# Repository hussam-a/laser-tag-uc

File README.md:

# laser-tag-uc
Microcontroller-based Laser Tag system

Authors:

Hussam A. El-Araby (github.com/hussam-a)

Mostafa Konsowa (github.com/konsowa)

Youssef Gaber (github.com/Gabrola)

Mennatallah Yahia

Ziad Osama

Project code and configurations are under the GNU GPL license (laser-tag-uc/LICENSE) 

# Project structure:

- Check files under folder project (laser-tag-uc/project)

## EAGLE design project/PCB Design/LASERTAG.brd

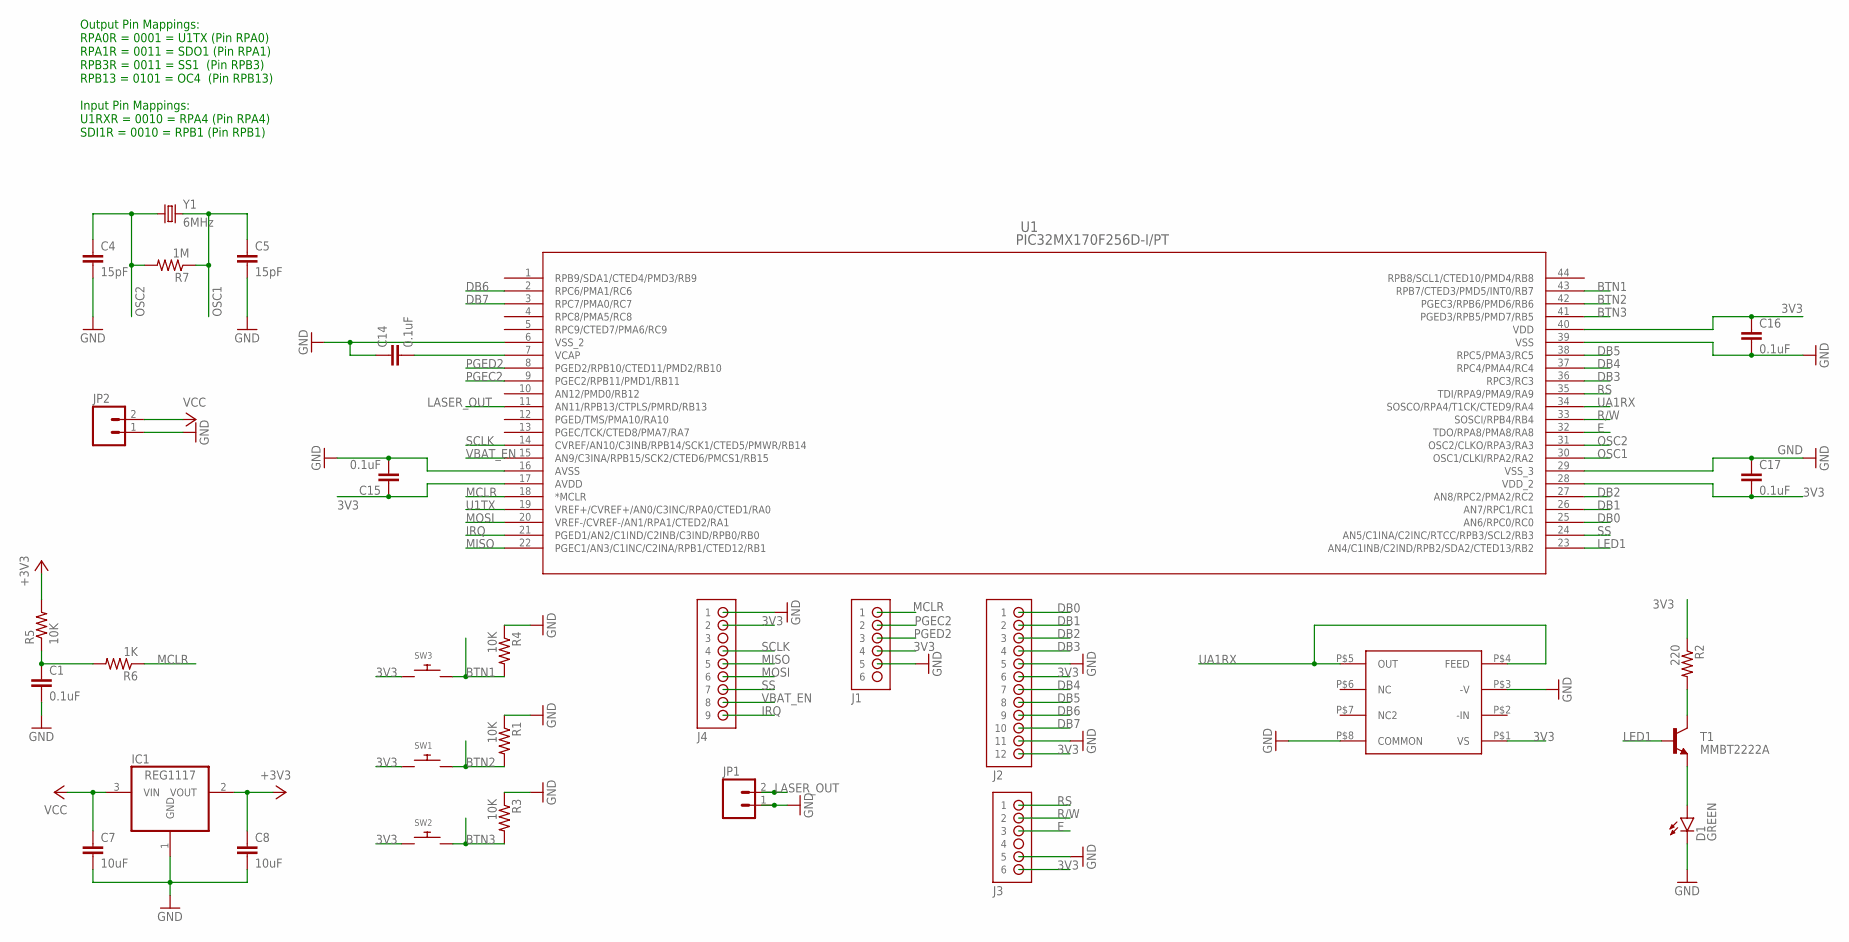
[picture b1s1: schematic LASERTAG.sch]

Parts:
C1, C14, C15, C16, C17: 0.1uF; 0603-CAP
C4, C5: 15pF; 0603-CAP
C7, C8: 10uF; 0603-CAP
D1: GREEN; LED-0603
IC1: REG1117; SOT223
IC3: OPT101P
J1, J3: HDR-1X6
J2: PMOD-2X6-P
J4: HDR-1X9
JP1, JP2: M02JST-PTH-2; JST-2-PTH
R1, R3, R4, R5: 10K; 0603-RES
R2: 220; 0603-RES
R6: 1K; 0603-RES
R7: 1M; 0603-RES
SW1, SW2, SW3: SWITCH_PUSHBUTTONC&K_KSS; BTN_CK_KSS
T1: MMBT2222A; SOT23
U1: PIC32MX170F256D-I/PT; TQFP44_10X10MC
Y1: 6MHz; HC49US

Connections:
3V3: C8.1, C15.1, C16.1, C17.2, IC1.2 (VOUT), IC3.P$1 (VS), J1.4, J2.6, J2.12, J3.6, J4.2, R2.1, R5.2, SW1.P$1, SW2.P$1, SW3.P$1, U1.17 (AVDD), U1.28 (VDD_2), U1.40 (VDD)
BTN1: R4.2, SW3.P$2, U1.43 (RPB7/CTED3/PMD5/INT0/RB7)
BTN2: R1.2, SW1.P$2, U1.42 (PGEC3/RPB6/PMD6/RB6)
BTN3: R3.2, SW2.P$2, U1.41 (PGED3/RPB5/PMD7/RB5)
DB0: J2.1, U1.25 (AN6/RPC0/RC0)
DB1: J2.2, U1.26 (AN7/RPC1/RC1)
DB2: J2.3, U1.27 (AN8/RPC2/PMA2/RC2)
DB3: J2.4, U1.36 (RPC3/RC3)
DB4: J2.7, U1.37 (RPC4/PMA4/RC4)
DB5: J2.8, U1.38 (RPC5/PMA3/RC5)
DB6: J2.9, U1.2 (RPC6/PMA1/RC6)
DB7: J2.10, U1.3 (RPC7/PMA0/RC7)
E: J3.3, U1.32 (TDO/RPA8/PMA8/RA8)
GND: C1.2, C4.2, C5.2, C7.2, C8.2, C14.1, C15.2, C16.2, C17.1, D1.C, IC1.1 (GND), IC3.P$3 (-V), IC3.P$8 (COMMON), J1.5, J2.5, J2.11, J3.5, J4.1, JP1.1, JP2.1, R1.1, R3.1, R4.1, U1.6 (VSS_2), U1.16 (AVSS), U1.29 (VSS_3), U1.39 (VSS)
IRQ: J4.9, U1.21 (PGED1/AN2/C1IND/C2INB/C3IND/RPB0/RB0)
LASER_OUT: JP1.2, U1.11 (AN11/RPB13/CTPLS/PMRD/RB13)
LED1: T1.1 (B), U1.23 (AN4/C1INB/C2IND/RPB2/SDA2/CTED13/RB2)
MCLR: J1.1, R6.1, U1.18 (*MCLR)
MISO: J4.5, U1.22 (PGEC1/AN3/C1INC/C2INA/RPB1/CTED12/RB1)
MOSI: J4.6, U1.20 (VREF-/CVREF-/AN1/RPA1/CTED2/RA1)
unnamed: C1.1, R5.1, R6.2
unnamed: C14.2, U1.7 (VCAP)
unnamed: R2.2, T1.3 (C)
unnamed: D1.A, T1.2 (E)
OSC1: C5.1, R7.1, U1.30 (OSC1/CLKI/RPA2/RA2), Y1.2
OSC2: C4.1, R7.2, U1.31 (OSC2/CLKO/RPA3/RA3), Y1.1
PGEC2: J1.2, U1.9 (PGEC2/RPB11/PMD1/RB11)
PGED2: J1.3, U1.8 (PGED2/RPB10/CTED11/PMD2/RB10)
R/W: J3.2, U1.33 (SOSCI/RPB4/RB4)
RS: J3.1, U1.35 (TDI/RPA9/PMA9/RA9)
SCLK: J4.4, U1.14 (CVREF/AN10/C3INB/RPB14/SCK1/CTED5/PMWR/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)
SS: J4.7, U1.24 (AN5/C1INA/C2INC/RTCC/RPB3/SCL2/RB3)
U1TX: U1.19 (VREF+/CVREF+/AN0/C3INC/RPA0/CTED1/RA0)
UA1RX: IC3.P$4 (FEED), IC3.P$5 (OUT), U1.34 (SOSCO/RPA4/T1CK/CTED9/RA4)
VBAT_EN: J4.8, U1.15 (AN9/C3INA/RPB15/SCK2/CTED6/PMCS1/RB15)
VCC: C7.1, IC1.3 (VIN), JP2.2

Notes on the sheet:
Output Pin Mappings: RPA0R = 0001 = U1TX (Pin RPA0) RPA1R = 0011 = SDO1 (Pin RPA1) RPB3R = 0011 = SS1 (Pin RPB3) RPB13 = 0101 = OC4 (Pin RPB13) Input Pin Mappings: U1RXR = 0010 = RPA4 (Pin RPA4) SDI1R = 0010 = RPB1 (Pin RPB1)

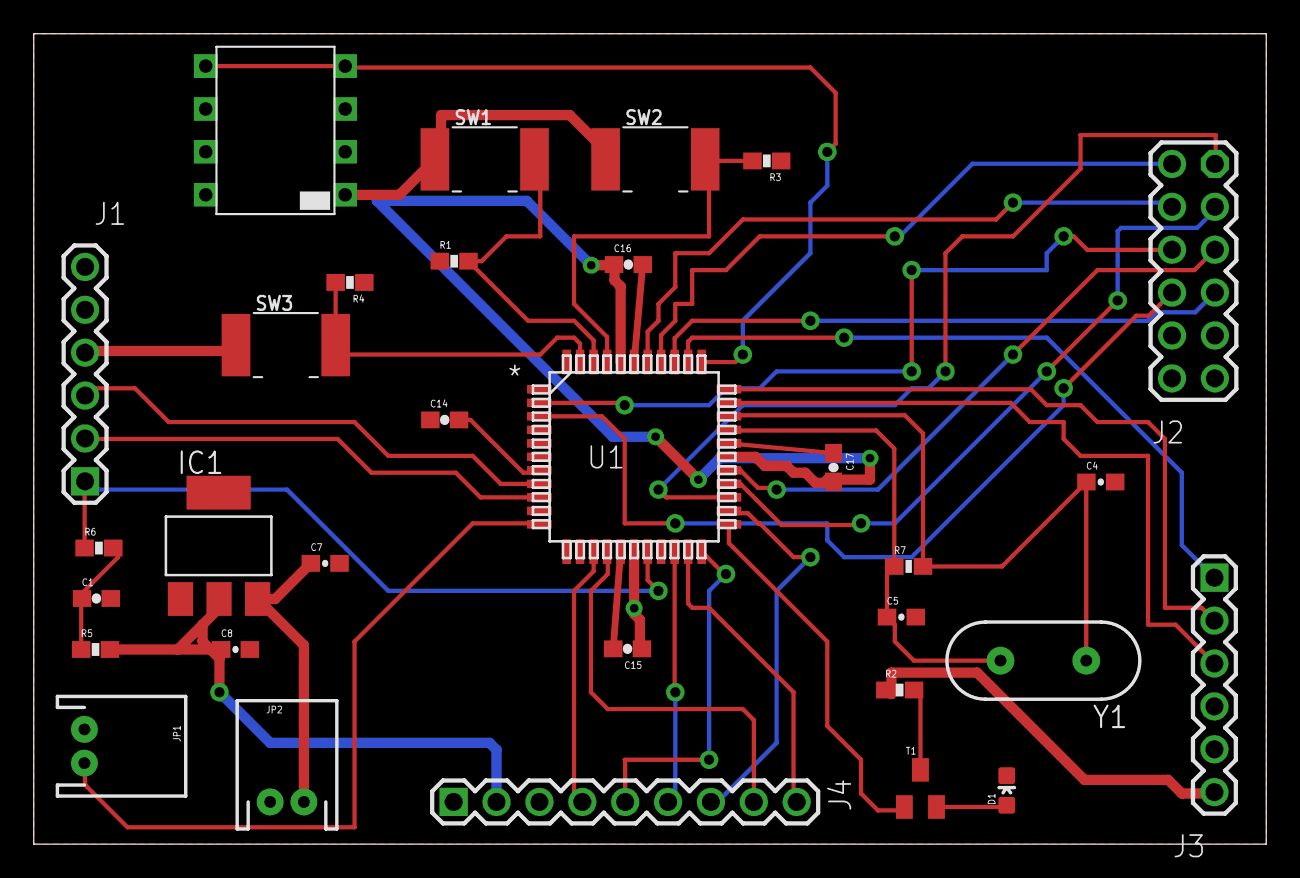
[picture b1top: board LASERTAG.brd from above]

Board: 2 copper layers, 73.0 x 48.0 mm, 31 parts (0 on the bottom side), 35 nets.

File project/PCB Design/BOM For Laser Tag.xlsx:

Designator | Value | Name | Description | Manufacturer | Manufacturer Part Number | Supplier | Supplier Part Number | Unit Price | Quantity | Total Price
U1 |  | PIC32MX170F256D-I/PT | IC MCU 32BIT 256KB FLASH 44TQFP | Microchip Technology | PIC32MX170F256D-I/PT | Digikey | PIC32MX170F256D-I/PT-ND | 3.8 | 1.0 | 3.8
 | 650nm | Laser Diode | 5mW 650nm Red | Adafruit | 1054.0 | Adafruit | 1054.0 | 5.95 | 1.0 | 5.95
IC3 |  | Laser Sensor | IC PHOTODIODE/AMPLIFIER 8DIP | Texas Instruments | OPT101P | Digikey | 296-23090-5-ND | 8.5 | 1.0 | 8.5
 |  | PMODCLP | PMODCLP PARALLEL LCD MODULE | Digilent, Inc. | 410-142P | Digikey | 1286-1035-ND | 37.99 | 1.0 | 37.99
 |  | CC3000 WiFi Breakout | Adafruit HUZZAH CC3000 WiFi Breakout | Adafruit | 1469.0 | Adafruit | 1469.0 | 34.95 | 1.0 | 34.95
D1 |  | SMD Green LED | LED GREEN CLEAR 0603 SMD | Lite-On Inc. | LTST-C191KGKT | Digikey | 160-1446-2-ND | 0.03636 | 1.0 | 0.03636
SW1, SW2, SW3 |  | Pushbutton Switch | SWITCH PUSH SPST-NO 0.1A 32V | C&K Components | D6C90 F1 LFS | Digikey | 401-1969-ND | 0.82 | 3.0 | 2.46
R2 | 220.0 | 220 Ohm SMD Resistor | RES SMD 220 OHM 5% 1/4W 0603 | Rohm Semiconductor | ESR03EZPJ221 | Digikey | RHM220DTR-ND | 0.00935 | 1.0 | 0.00935
R1, R3, R4, R5 | 10k | 10K Ohm SMD Resistor | RES SMD 10K OHM 1% 1/4W 0603 | Rohm Semiconductor | ESR03EZPF1002 | Digikey | RHM10KADTR-ND | 0.0136 | 3.0 | 0.0408
C1, C14, C15, C16, C17 | 0.1uF | CAP0603-CAP | Capacitor | Murata Electronics North America | GQM1885C2AR10BB01D | Digikey | 490-4835-2-ND | 0.15195 | 5.0 | 0.75975
R6 | 1K | 1K Ohm SMD Resistor | RES SMD 1K OHM 5% 1/4W 0603 | Rohm Semiconductor | ESR03EZPJ102 | Digikey | RHM1.0KDTR-ND | 0.00935 | 1.0 | 0.00935
R7 | 1M | SMD Resistor | RES SMD 1M OHM 5% 1/4W 0603 | Rohm Semiconductor | ESR03EZPJ105 | Digikey | RHM1MDCT-ND | 0.1 | 1.0 | 0.1
Y1 | 6MHz | 6MHz Crystal Oscillator | Crystal 6MHz 18pF HC49/US | Abracon LLC | ABL-6.000MHZ-B2 | Digikey | 535-9060-ND | 0.176 | 1.0 | 0.176
C4, C5 | 15pF | 15pF SMD Ceramic Capacitor | CAP CER 15PF 50V NP0 0603 | Samsung Electro-Mechanics America, Inc. | CL10C150JB8NNND | Digikey | CL10C150JB8NNND-ND | 0.00172 | 2.0 | 0.00344
C7, C8 | 10uF | 10uF SMD Ceramic Capacitor | CAP CER 10UF 10V X5R 0603 | Samsung Electro-Mechanics America, Inc. | CL10A106KP8NNND | Digikey | CL10A106KP8NNND-ND | 0.02266 | 2.0 | 0.04532
IC1 |  | 3.3V Linear Voltage Regulator | IC REG LDO 3.3V 1A SOT223-3 | Diodes Incorporated | AP1117E33G-13 | Digikey | AP1117E33GDITR-ND | 0.12854 | 1.0 | 0.12854
T1 |  | MMBT2222A Transistor | TRANS NPN 40V 0.6A SOT23 | ON Semiconductor | MMBT2222ALT1G | Digikey | MMBT2222ALT1GOSTR-ND | 0.01811 | 1.0 | 0.01811
J1 |  | 1x6 Female Pin Header | Connector Header 6 Position 0.100" | Sullins Connector Solutions | PPPC061LFBN-RC | Digikey | S7039-ND | 0.7 | 1.0 | 0.7
J3 |  | 1x6 Male Pin Header | SIL VERTICAL PC TAIL PIN HEADER | Harwin Inc. | M20-9990645 | Digikey | 952-2269-ND | 0.26 | 1.0 | 0.26
J2 |  | 2x6 Male Pin Header | DIL VERTICAL PC TAIL PIN HEADER | Harwin Inc. | M20-9980645 | Digikey | 952-2125-ND | 0.42 | 1.0 | 0.42
J4 |  | 1x9 Female Pin Header | Connector Header 9 Position 0.100" | Sullins Connector Solutions | PPPC091LFBN-RC | Digikey | S7042-ND | 0.83 | 1.0 | 0.83
JP1, JP2 |  | 2-Pin JST Connector | CONN HEADER PH SIDE 2POS 2MM | JST Sales America Inc. | S2B-PH-K-S(LF)(SN) | Digikey | 455-1719-ND | 0.16 | 2.0 | 0.32
 |  |  |  |  |  |  | Totals |  | 13 | 94.49626

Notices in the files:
parts and their libraries:
SparkFun-LED: Licensing: Creative Commons ShareAlike 4.0 International - https://creativecommons.org/licenses/by-sa/4.0
SparkFun: Licensing: CC v3.0 Share-Alike You are welcome to use this library for commercial purposes.
